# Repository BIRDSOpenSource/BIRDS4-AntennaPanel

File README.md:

<div align="center">
  
</div>

# BIRDS4-AntennaPanel
 Documentation for the Antenna Panel used in the BIRDS4 satellite.

Inside the different folders are the Eagle files used in different satellites of the BIRDS 4 generation. Differences are mainly aesthetic (ie. logos and such).

## About the BIRDS4 Program:

The Mission Statement of the Project is:

> “By successfully building and operating first satellite of nation, advance toward indigenous space program in each country”

The project is led by Kyushu Institute of Technology in Japan and involves students from Philippines, Paraguay, Nepal, Turkey and Japan.

Satellite Names: Tsuru (Japan), Guarani-1 (Paraguay) and Maya-2 (Phillipines)

Stakeholders:  Paraguayan Space Agency, Polytechnic Faculty of National University of Asuncion, and Kyushu Institute of Technology (Kyutech) for Japan.

Project duration: 2018-2022

CubeSat: 1U (10x10x10) cm3

Weight: 1.13kg

Launch Date: 21st February 2021 

BIRDS-4 has 1 main missions in total; APRS Store and forward mission

## Organisation structure

```bash

├── .gitattributes
├── AntennaPanel_Partslist.xlsx
├── FM_GuaraniSat
│   ├── BIRDS4_-Y_panel_FM_GUARANI_v3.brd
│   └── BIRDS4_-Y_panel_FM_GUARANI_v3.sch
├── FM_MAYA-2
│   ├── BIRDS4_-Y_panel_FM_MAYA-2_v6.brd
│   └── BIRDS4_-Y_panel_FM_MAYA-2_v6.sch
├── FM_TSURU
│   ├── BIRDS4_-Y_panel_FM_TSURU_v2.brd
│   └── BIRDS4_-Y_panel_FM_TSURU_v2.sch
├── LICENSE
├── README.md
├── mount_bottom.pdf
└── mount_top.pdf

```
> [!CAUTION]
> The files `.sch` and `.brd` files in this repositiry were created using Eagle software.
 
For those that want to import these files into 
KiCAD7 [here's how you do it](https://community.element14.com/technologies/open-source-hardware/b/blog/posts/working-with-kicad-7-importing-eagle-files) 
 or KiCAD5.1 [here's how you do it](https://www.youtube.com/watch?v=RBc02MwpKxk&t=1s).

## Features

## I like this project, can I help you?
You are welcome 🙂

* Give us a star ⭐
* Watch repository to be notified about updates 👀
* If you will find some errors, report them in Issues 🐞
* Try Birds designs on some real computer and let us know how it worked in Discussions. 💬
* We would greatly appreciate if you would also tell others about this ecosystem, it helps us to improve BIRDS Open Source. Thank you!

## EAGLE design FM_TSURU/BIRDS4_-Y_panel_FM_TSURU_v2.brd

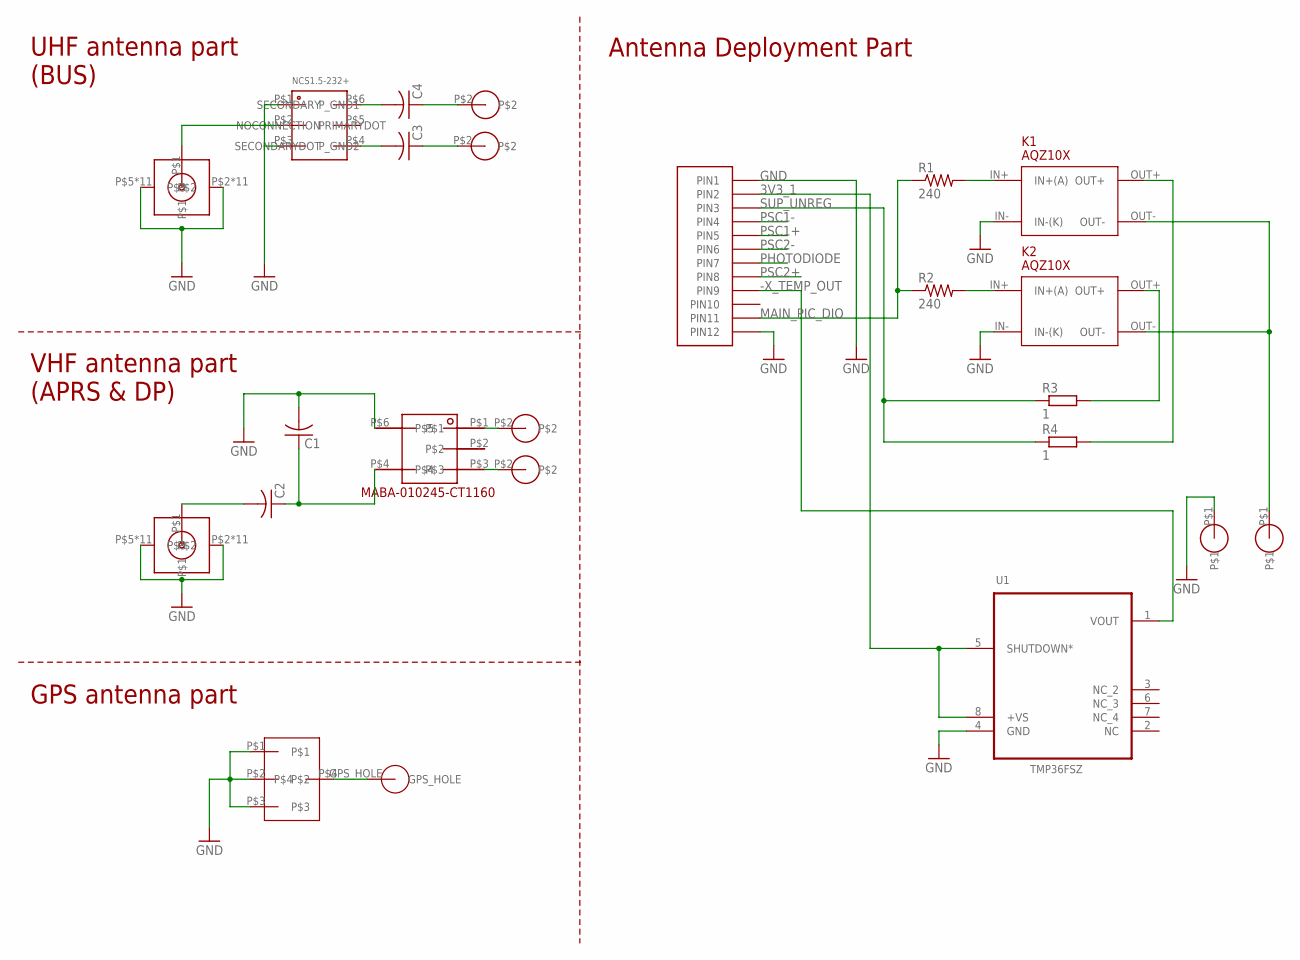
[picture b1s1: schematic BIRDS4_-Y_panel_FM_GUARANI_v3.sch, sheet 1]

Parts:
C1, C2, C3, C4: C-USC1608; C1608
HOLE1, HOLE2: B4_FOR_NEW_DIPOLE
HOLE7: GPS_HOLE
J1, J2: SMA_142_0711_301
J3: MMCX_GPS
J5: HEADER12PIN
K1, K2: AQZ10X
NCS1: NCS1.5-232+
R1, R2: 240; R0402
R3, R4: 1; R1218
U1: TMP36FSZ; SOIC_N
U$1, U$5: NICR_HOLE
U$2: MABA-010245-CT1160
U$3, U$4: B4_FOR_NEW_DIPOLE

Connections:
3V3_1: J5.P2 (PIN2), U1.5 (SHUTDOWN*), U1.8 (+VS); also elsewhere on the board
-X_TEMP_OUT: J5.P9 (PIN9), U1.1 (VOUT)
GND: C1.2, J1.P$2, J1.P$3, J1.P$4, J1.P$5, J1.P$6, J1.P$7, J1.P$8, J1.P$9, J1.P$10, J1.P$11, J1.P$12, J1.P$13, J1.P$14, J1.P$15, J1.P$16, J1.P$17, J1.P$18, J1.P$19, J1.P$20, J1.P$21, J1.P$22, J1.P$23, J2.P$2, J2.P$3, J2.P$4, J2.P$5, J2.P$6, J2.P$7, J2.P$8, J2.P$9, J2.P$10, J2.P$11, J2.P$12, J2.P$13, J2.P$14, J2.P$15, J2.P$16, J2.P$17, J2.P$18, J2.P$19, J2.P$20, J2.P$21, J2.P$22, J2.P$23, J3.P$1, J3.P$2, J3.P$3, J5.P1 (PIN1), J5.P12 (PIN12), K1.IN- (IN-(K)), K2.IN- (IN-(K)), NCS1.P$1 (P_GND1), NCS1.P$3 (P_GND2), U1.4 (GND), U$2.P$6, U$5.P$1; also elsewhere on the board
HOT: K1.OUT-, K2.OUT-, U$1.P$1
MAIN_PIC_DIO: J5.P11 (PIN11), R1.1, R2.1
unnamed: K1.IN+ (IN+(A)), R1.2
unnamed: K1.OUT+, R4.2
unnamed: K2.IN+ (IN+(A)), R2.2
unnamed: C4.1, HOLE2.P$2
unnamed: C2.2, J2.P$1
unnamed: C1.1, C2.1, U$2.P$4
unnamed: U$2.P$1, U$3.P$2
unnamed: U$2.P$3, U$4.P$2
unnamed: C3.1, HOLE1.P$2
unnamed: C4.2, NCS1.P$6 (SECONDARY)
unnamed: C3.2, NCS1.P$4 (SECONDARYDOT)
unnamed: J1.P$1, NCS1.P$2 (PRIMARYDOT)
unnamed: K2.OUT+, R3.2
unnamed: HOLE7.GPS_HOLE, J3.P$4
PHOTODIODE: J5.P7 (PIN7); also elsewhere on the board
PSC1+: J5.P5 (PIN5); also elsewhere on the board
PSC1-: J5.P4 (PIN4); also elsewhere on the board
PSC2+: J5.P8 (PIN8); also elsewhere on the board
PSC2-: J5.P6 (PIN6); also elsewhere on the board
SUP_UNREG: J5.P3 (PIN3), R3.1, R4.1

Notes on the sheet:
UHF antenna part (BUS)
VHF antenna part (APRS & DP)
GPS antenna part
Antenna Deployment Part

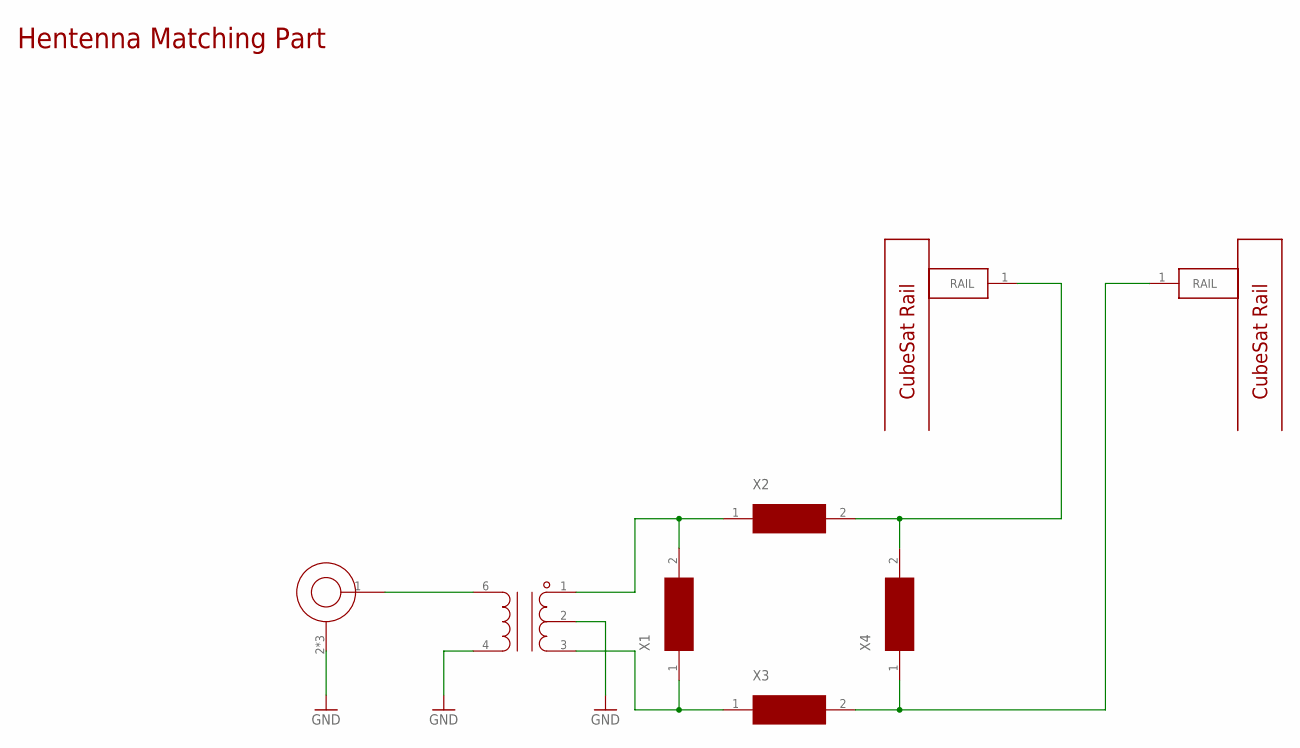
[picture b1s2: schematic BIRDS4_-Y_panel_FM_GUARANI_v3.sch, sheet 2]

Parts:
HOLE8, HOLE9: CUBESAT_RAIL; HOLE
J4: HNT RF CON; R302302000
T3: TC1-1T+; TC1.5-52T+
X1, X2, X3, X4: PASSIVECOMPONENT1608; C1608

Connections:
GND: J4.2 (GND), J4.3 (GND), J4.4 (GND), T3.2, T3.4; also elsewhere on the board
unnamed: T3.1, X1.2, X2.1
unnamed: T3.3, X1.1, X3.1
unnamed: J4.1 (LINE), T3.6
unnamed: HOLE8.1, X2.2, X4.2
unnamed: HOLE9.1, X3.2, X4.1

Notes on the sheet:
Hentenna Matching Part

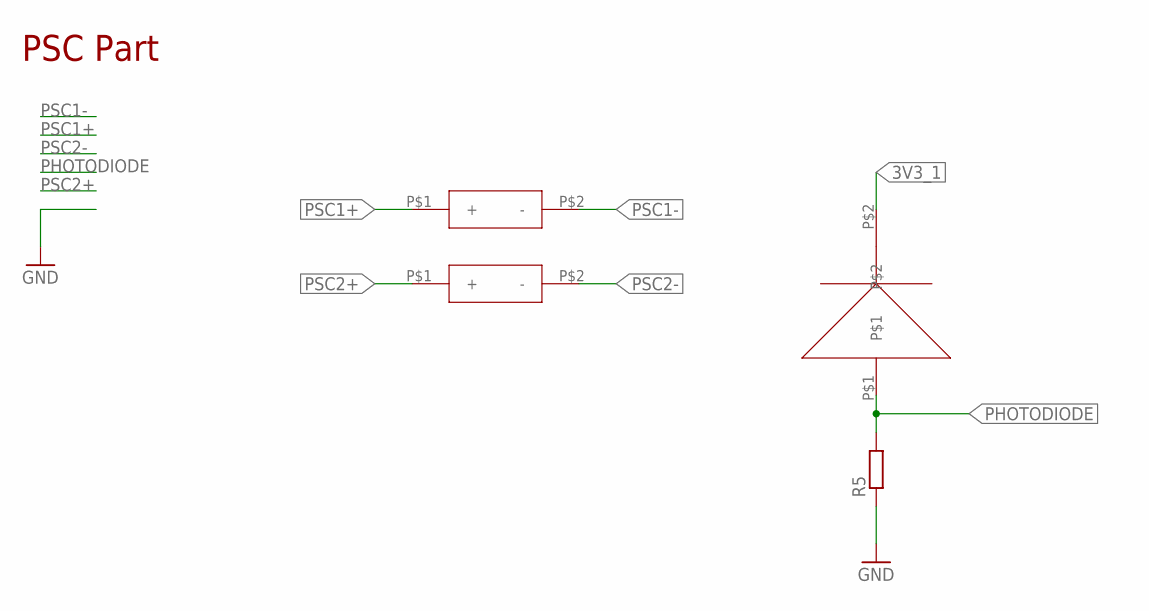
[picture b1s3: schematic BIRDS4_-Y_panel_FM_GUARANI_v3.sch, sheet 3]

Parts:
D1: SFH2430
R5: R-EU_R0805; R0805
S1, S2: PEROVSKITE

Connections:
3V3_1: D1.P$2; also elsewhere on the board
GND: R5.1; also elsewhere on the board
PHOTODIODE: D1.P$1, R5.2; also elsewhere on the board
PSC1+: S1.P$1 (+); also elsewhere on the board
PSC1-: S1.P$2 (-); also elsewhere on the board
PSC2+: S2.P$1 (+); also elsewhere on the board
PSC2-: S2.P$2 (-); also elsewhere on the board

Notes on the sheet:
PSC Part

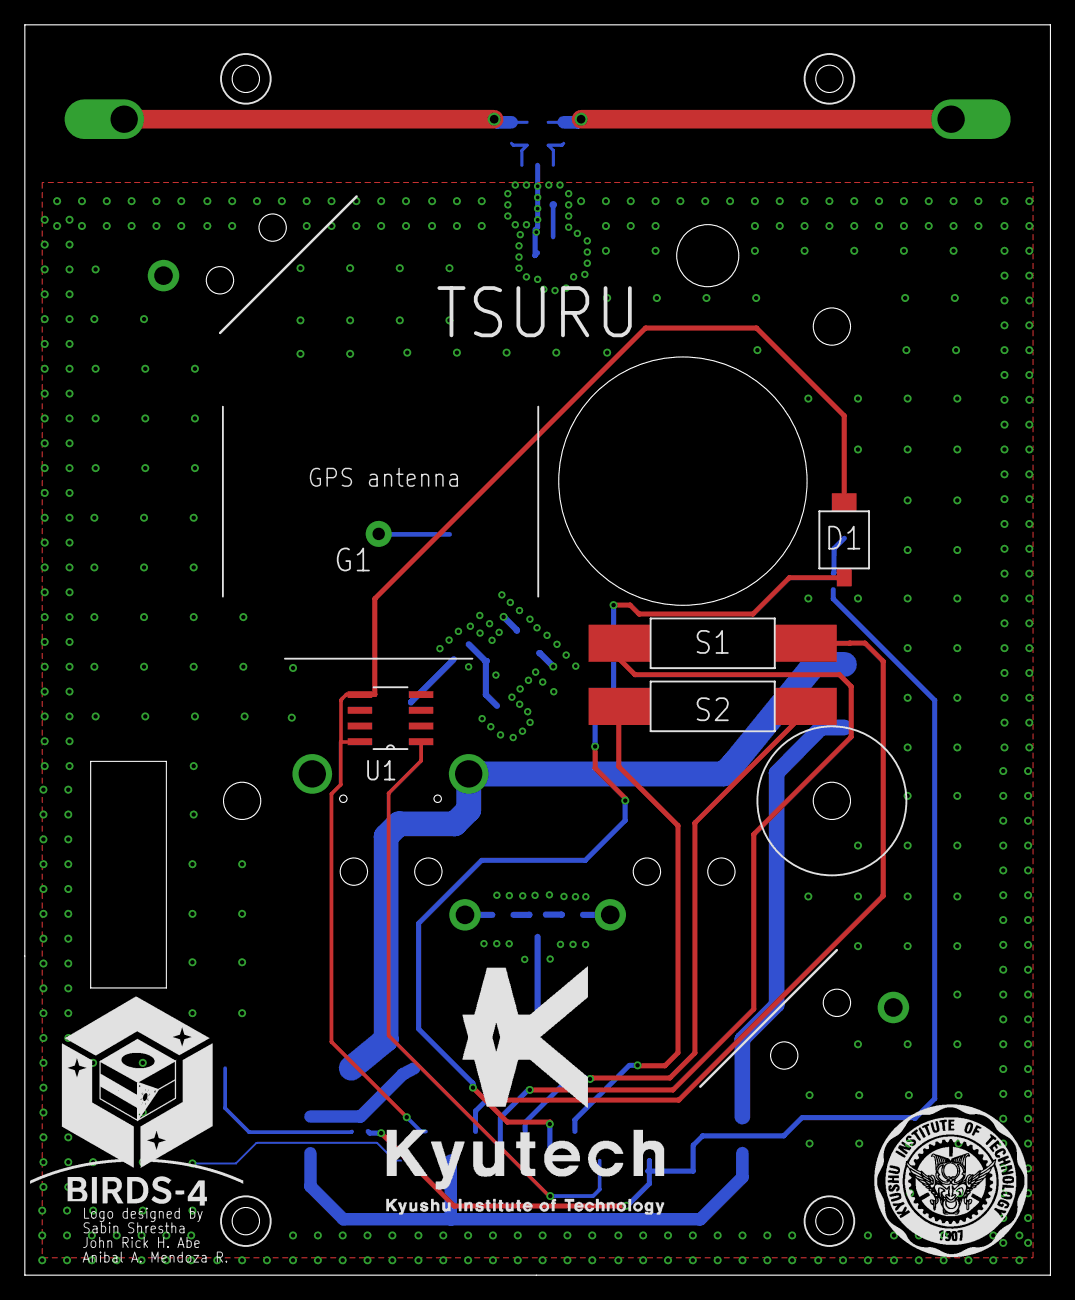
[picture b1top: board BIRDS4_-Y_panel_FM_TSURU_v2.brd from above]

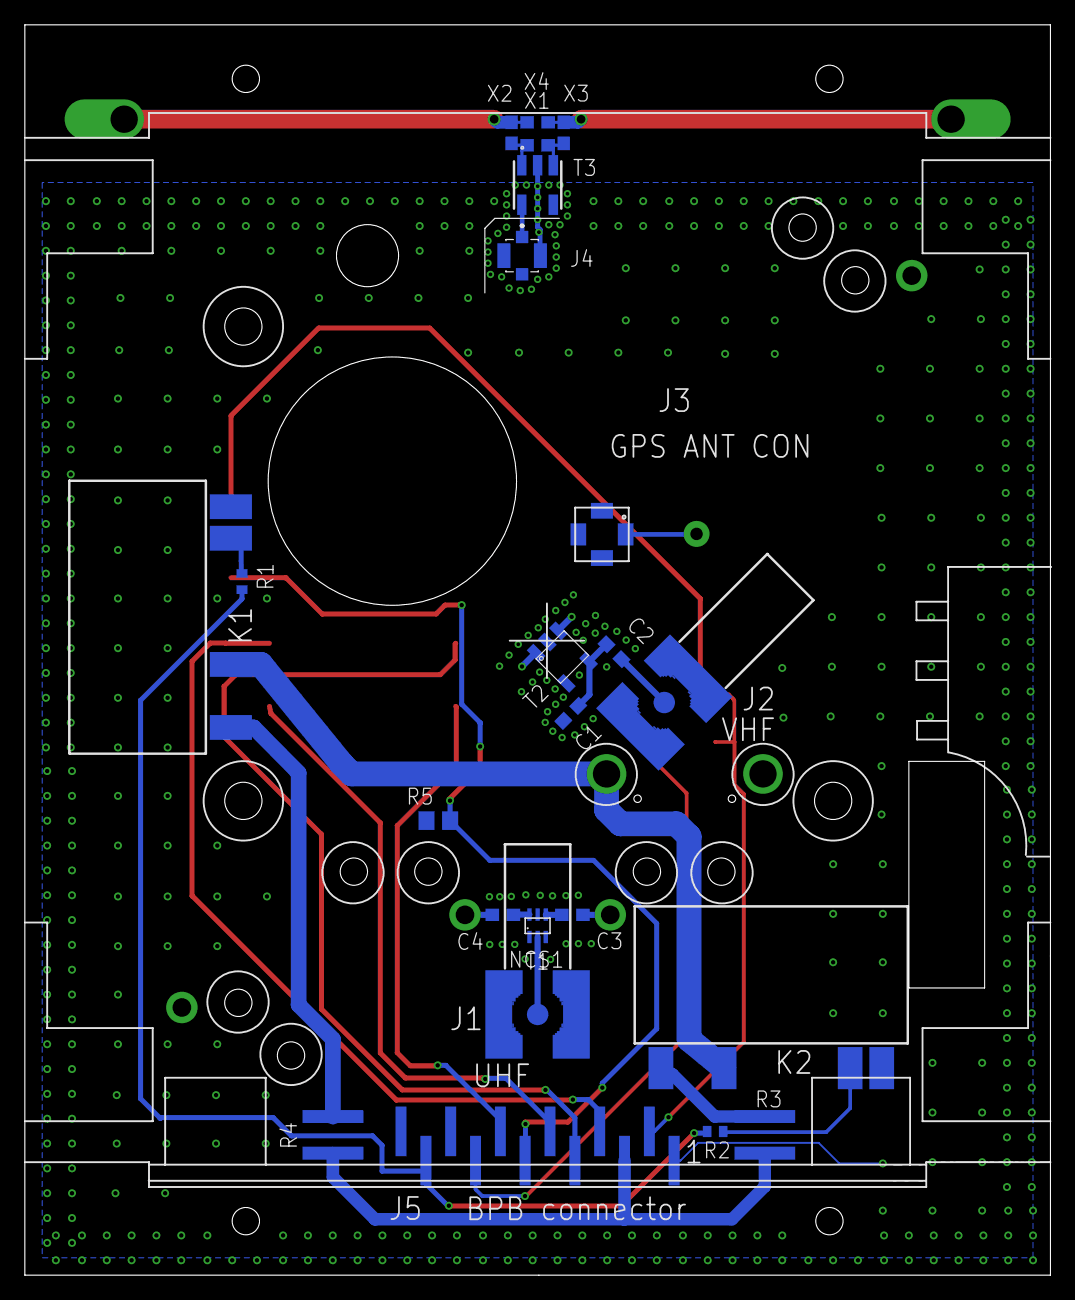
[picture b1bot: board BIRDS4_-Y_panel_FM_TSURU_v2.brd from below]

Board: 4 copper layers, 82.6 x 100.7 mm, 36 parts (26 on the bottom side), 30 nets.
